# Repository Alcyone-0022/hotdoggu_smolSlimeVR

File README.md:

# hotdoggu_smolSlimeVR
KiCad project - slimevr tracker using  ESP32-C3-MINI-1, LSM6DSV16X    
Includes 3d-printable case **(for 34\*50\*10(H) Li-Polymer battery)**
# Used Components
### BOM for hotdoggu_smolSlimeVR

| Comment | Designator | Footprint | LCSC | Quantity |
|---------|------------|-----------|------|----------|
| 10k | R13,R14,R17,R18 | R_0603_1608Metric | C15401 | 4 |
| TYPE-C-31-M-12 | J1 | USB_C_Receptacle_GCT_USB4105-xx-A_16P_TopMnt_Horizontal | C165948 | 1 |
| 1k | R11,R12,R15,R16 | R_0603_1608Metric | C21190 | 4 |
| JS202011CQN | SW1 | SW_CK_JS202011CQN_DPDT_Straight | C221663 | 1 |
| 53261-0271 | J2 | Molex_PicoBlade_53261-0271_1x02-1MP_P1.25mm_Horizontal | C225111 | 1 |
| LED,0603,Red | LED1 | LED_0603_1608Metric | C2286 | 1 |
| 0603,White | LED3 | LED_0603_1608Metric | C2290 | 1 |
| 5.1k, 1% | R2,R3,R5 | R_0603_1608Metric | C23186 | 3 |
| ESP32-C3-MINI-1-H4 | U1 | ESP32-C3-MINI-1 | C2934569 | 1 |
| 2k | R19 | R_0603_1608Metric | C4190 | 1 |
| MCP73831-2-OT | U3 | SOT-23-5 | C424093 | 1 |
| LSM6DSV16X | U2 | LGA-14_3x2.5mm_P0.5mm_LayoutBorder3x4y | C5267406 | 1 |
| 100nF | C5,C6,C7,C8 | C_0603_1608Metric | C66501 | 4 |
| 0603,Yellow | LED2 | LED_0603_1608Metric | C72038 | 1 |
| TS-1088-AR02016 | SW2,SW3 | TS-1088-AR02016 | C720477 | 2 |
| LP5907MFX-3.3 | U4 | SOT-23-5 | C80670 | 1 |
| 10uF | C1,C2 | C_0603_1608Metric | C96446 | 2 |    
### Battery
|Component|Description|Link|
|---------|-----------|----|
|DTP103450|3.7V 1800mAh Li-Polymer battery 34\*50\*10(H)| https://www.devicemart.co.kr/goods/view?no=15285794|
# slimeVR Configuration
**platformio.ini**
```ini
[env:esp32c3]
platform = espressif32 @ 6.7.0
platform_packages =
 framework-arduinoespressif32 @ https://github.com/espressif/arduino-esp32.git#3.0.1
 framework-arduinoespressif32-libs @ https://github.com/espressif/arduino-esp32/releases/download/3.0.1/esp32-arduino-libs-3.0.1.zip
build_flags =
 ${env.build_flags}
 -DESP32C3
board = lolin_c3_mini
```
    
**defines.h**
```C
#define IMU IMU_LSM6DSV
#define SECOND_IMU IMU
#define BOARD BOARD_CUSTOM
#define IMU_ROTATION DEG_0
#define SECOND_IMU_ROTATION DEG_0
#define PRIMARY_IMU_OPTIONAL false
#define SECONDARY_IMU_OPTIONAL true
#define MAX_IMU_COUNT 1
#ifndef IMU_DESC_LIST
#define IMU_DESC_LIST \
    IMU_DESC_ENTRY(IMU,        PRIMARY_IMU_ADDRESS_TWO,   IMU_ROTATION,        PIN_IMU_SCL, PIN_IMU_SDA, PRIMARY_IMU_OPTIONAL, PIN_IMU_INT)
#endif
#define BATTERY_MONITOR BAT_EXTERNAL
#elif BOARD == BOARD_CUSTOM
#define LED_PIN 10
#define LED_INVERTED false
#define PIN_IMU_SDA 3
#define PIN_IMU_SCL 4
#define PIN_IMU_INT 255
#define PIN_IMU_INT_2 255
#define PIN_BATTERY_LEVEL 0
#define BATTERY_SHIELD_RESISTANCE 0
#define BATTERY_SHIELD_R1 1000
#define BATTERY_SHIELD_R2 1000
```

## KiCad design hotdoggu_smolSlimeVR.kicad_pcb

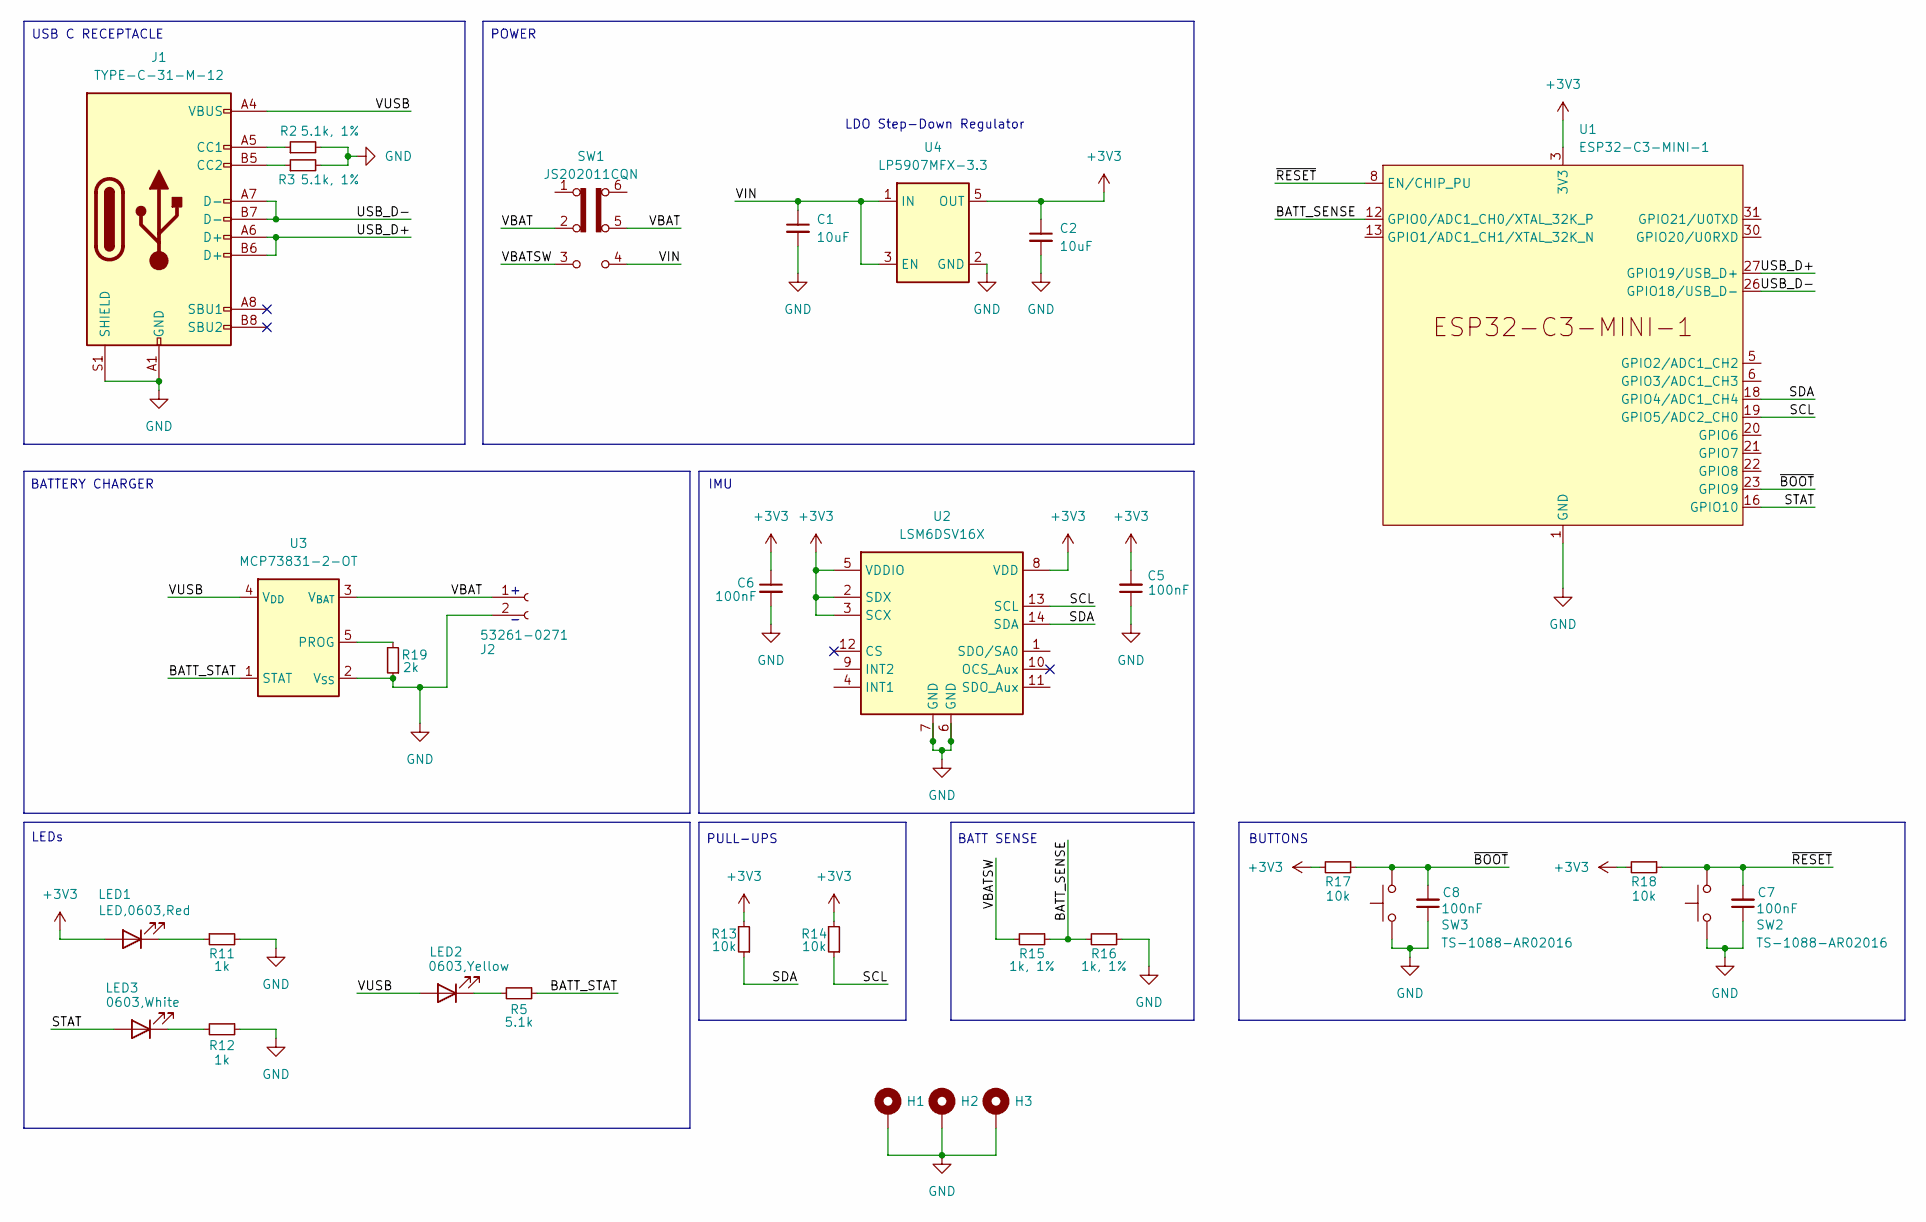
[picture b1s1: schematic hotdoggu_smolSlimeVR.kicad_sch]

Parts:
C1, C2: 10uF; C_0603_1608Metric
C5, C6, C7, C8: 100nF; C_0603_1608Metric
H1, H2, H3: MountingHole; MountingHole_2.2mm_M2_DIN965_Pad_TopBottom
J1: TYPE-C-31-M-12; USB_C_Receptacle_GCT_USB4105-xx-A_16P_TopMnt_Horizontal
J2: 53261-0271; Molex_PicoBlade_53261-0271_1x02-1MP_P1.25mm_Horizontal
LED1: LED,0603,Red; LED_0603_1608Metric
LED2: 0603,Yellow; LED_0603_1608Metric
LED3: 0603,White; LED_0603_1608Metric
R2, R3: 5.1k, 1%; R_0603_1608Metric
R5: 5.1k; R_0603_1608Metric
R11, R12: 1k; R_0603_1608Metric
R13, R14, R17, R18: 10k; R_0603_1608Metric
R15, R16: 1k, 1%; R_0603_1608Metric
R19: 2k; R_0603_1608Metric
SW1: JS202011CQN; SW_CK_JS202011CQN_DPDT_Straight
SW2, SW3: TS-1088-AR02016
U1: ESP32-C3-MINI-1
U2: LSM6DSV16X; LGA-14_3x2.5mm_P0.5mm_LayoutBorder3x4y
U3: MCP73831-2-OT; SOT-23-5
U4: LP5907MFX-3.3; SOT-23-5

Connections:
+3V3: C2.1, C5.2, C6.1, LED1.2 (A), R13.2, R14.2, R17.2, R18.2, U1.3 (3V3), U2.2 (SDX), U2.3 (SCX), U2.5 (VDDIO), U2.8 (VDD), U4.5 (OUT)
/BATT_SENSE: R15.1, R16.2, U1.12 (GPIO0/ADC1_CH0/XTAL_32K_P)
/BATT_STAT: R5.1, U3.1 (STAT)
/SCL: R14.1, U1.19 (GPIO5/ADC2_CH0), U2.13 (SCL)
/SDA: R13.1, U1.18 (GPIO4/ADC1_CH4), U2.14 (SDA)
/STAT: LED3.2 (A), U1.16 (GPIO10)
/USB_D+: J1.A6 (D+), J1.B6 (D+), U1.27 (GPIO19/USB_D+)
/USB_D-: J1.A7 (D-), J1.B7 (D-), U1.26 (GPIO18/USB_D-)
/VBAT: J2.1, SW1.2 (B), SW1.5 (B), U3.3 (V_{BAT})
/VBATSW: R15.2, SW1.3 (C)
/VIN: C1.1, SW1.4 (A), U4.1 (IN), U4.3 (EN)
/VUSB: J1.A4 (VBUS), J1.A9 (VBUS), J1.B4 (VBUS), J1.B9 (VBUS), LED2.2 (A), U3.4 (V_{DD})
/~BOOT: C8.2, R17.1, SW3.2, U1.23 (GPIO9)
/~RESET: C7.2, R18.1, SW2.2, U1.8 (EN/CHIP_PU)
GND: C1.2, C2.2, C5.1, C6.2, C7.1, C8.1, H1.1, H2.1, H3.1, J1.A1 (GND), J1.A12 (GND), J1.B1 (GND), J1.B12 (GND), J1.S1 (SHIELD), J2.2, R2.2, R3.2, R11.2, R12.1, R16.1, R19.1, SW2.1, SW3.1, U1.1 (GND), U1.2 (GND), U1.11 (GND), U1.14 (GND), U1.36 (GND), U1.37 (GND), U1.38 (GND), U1.39 (GND), U1.40 (GND), U1.41 (GND), U1.42 (GND), U1.43 (GND), U1.44 (GND), U1.45 (GND), U1.46 (GND), U1.47 (GND), U1.48 (GND), U1.49 (GND), U1.50 (GND), U1.51 (GND), U1.52 (GND), U1.53 (GND), U2.6 (GND), U2.7 (GND), U3.2 (V_{SS}), U4.2 (GND)
unnamed: J1.A5 (CC1), R2.1
unnamed: J1.B5 (CC2), R3.1
unnamed: LED1.1 (K), R11.1
unnamed: LED2.1 (K), R5.2
unnamed: LED3.1 (K), R12.2
unnamed: R19.2, U3.5 (PROG)

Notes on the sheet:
USB C RECEPTACLE
BATTERY CHARGER
LEDs
IMU
POWER
BUTTONS
PULL-UPS
LDO Step-Down Regulator
+ -
BATT SENSE

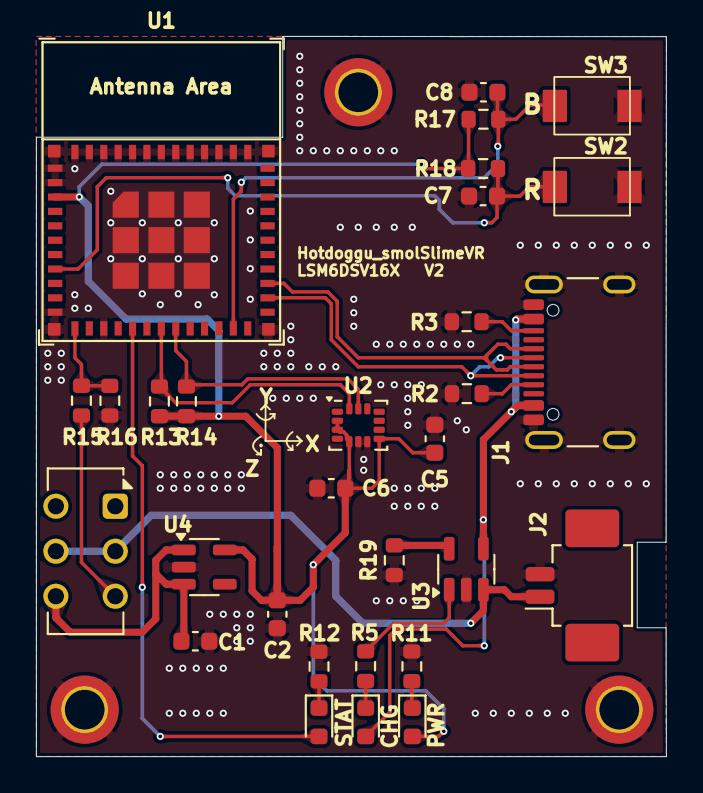
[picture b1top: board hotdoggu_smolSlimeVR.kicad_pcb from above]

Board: 2 copper layers, 35.0 x 40.0 mm, 33 parts (0 on the bottom side), 21 nets.

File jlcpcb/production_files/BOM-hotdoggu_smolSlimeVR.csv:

Comment,Designator,Footprint,LCSC,Quantity
10k,"R13,R14,R17,R18",R_0603_1608Metric,C15401,4
TYPE-C-31-M-12,J1,USB_C_Receptacle_GCT_USB4105-xx-A_16P_TopMnt_Horizontal,C165948,1
1k,"R11,R12,R15,R16",R_0603_1608Metric,C21190,4
JS202011CQN,SW1,SW_CK_JS202011CQN_DPDT_Straight,C221663,1
53261-0271,J2,Molex_PicoBlade_53261-0271_1x02-1MP_P1.25mm_Horizontal,C225111,1
"LED,0603,Red",LED1,LED_0603_1608Metric,C2286,1
"0603,White",LED3,LED_0603_1608Metric,C2290,1
"5.1k, 1%","R2,R3,R5",R_0603_1608Metric,C23186,3
ESP32-C3-MINI-1,U1,ESP32-C3-MINI-1,C2934569,1
2k,R19,R_0603_1608Metric,C4190,1
MCP73831-2-OT,U3,SOT-23-5,C424093,1
LSM6DSV16X,U2,LGA-14_3x2.5mm_P0.5mm_LayoutBorder3x4y,C5267406,1
100nF,"C5,C6,C7,C8",C_0603_1608Metric,C66501,4
"0603,Yellow",LED2,LED_0603_1608Metric,C72038,1
TS-1088-AR02016,"SW2,SW3",TS-1088-AR02016,C720477,2
LP5907MFX-3.3,U4,SOT-23-5,C80670,1
10uF,"C1,C2",C_0603_1608Metric,C96446,2

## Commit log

2025-03-07 initial commit, rev 1
2025-03-28 Hotdoggu_smolSlimeVR V2
2025-04-02 update readme img
2025-04-09 change img
